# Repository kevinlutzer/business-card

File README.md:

# Electronic Business Card 

The purpose of this project was to demonstrate some of my skills as an Electrical Engineer to potential employers. This project required me to build and prototype a tri-state circuit, add controls with a STM32G ARM microcontroller and design/manufacture a custom printed circuit board. When you plug the device into a standard USB2A port it scrolls my portfolio website's URL across the matrix display. I designed this device to cost about $2.50 CAD per populated board. 

This idea was inspired by a piece of advice that Dave Jones, the owner of the [EEVblog](https://www.eevblog.com/) gave. He suggests that engineers should be bringing something to an interview to show that they can actually design and build things. I sent a later version of this project to Dave Jones with a programmer PCB which he opened on a [Mailbag Segment](https://youtu.be/45C6HFf2kIA?si=SCQMgJs3VvQc_wUq&t=3084). 

Currently I am using the project as a way to test and calibrate a pick and place machine.

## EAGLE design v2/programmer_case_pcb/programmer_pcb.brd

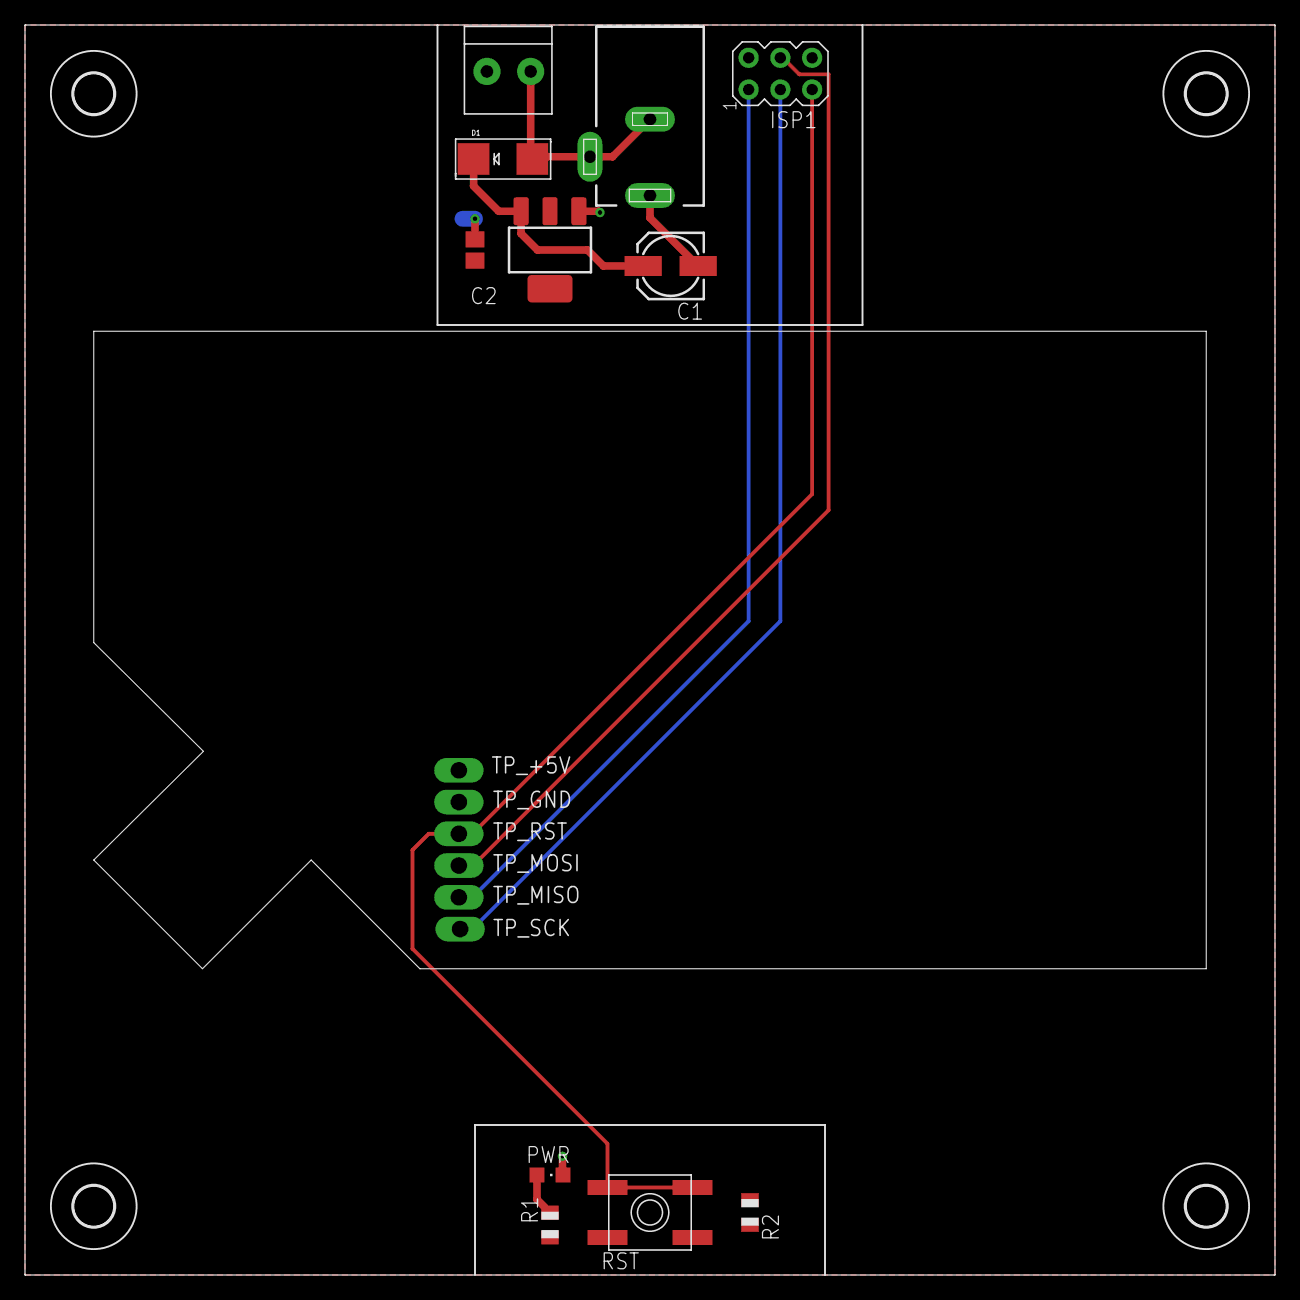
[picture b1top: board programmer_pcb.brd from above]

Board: 2 copper layers, 100.0 x 100.0 mm, 21 parts (0 on the bottom side), 9 nets.

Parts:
5VREG: LD1117; SOT223
C1: 0.33u; 153CLV-0505
C2: 0.1u; C0805
D1: SMADIODE
H1, H2, H3, H4: MOUNT-HOLE3.2; 3,2
ISP1: AVRISP-6; AVRISP
J1: 1X2-3.5MM
J2: DCJ0303
PWR: CHIPLED_0805
R1: 10K; R0805
R2: 220; R0805
RST: SPST_TACT-EVQQ2; EVQ-Q2
TP_+5V: TPSQPAD1-13Y; P1-13Y
TP_GND: TPSQPAD1-13Y; P1-13Y
TP_MISO: TPSQPAD1-13Y; P1-13Y
TP_MOSI: TPSQPAD1-13Y; P1-13Y
TP_RST: TPSQPAD1-13Y; P1-13Y
TP_SCK: TPSQPAD1-13Y; P1-13Y

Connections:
+5V: 5VREG.2, 5VREG.4, C2.1, ISP1.2, R1.2, R2.2, TP_+5V.TP
GND: 5VREG.1, C1.-, C2.2, ISP1.6, J1.1, J2.1, PWR.C, RST.A, RST.A', TP_GND.TP
MISO: ISP1.1, TP_MISO.TP
MOSI: ISP1.4, TP_MOSI.TP
unnamed: PWR.A, R1.1
unnamed: D1.A, J1.2, J2.2, J2.3
RESET: ISP1.5, R2.1, RST.B, RST.B', TP_RST.TP
SCK: ISP1.3, TP_SCK.TP
V+: 5VREG.3, C1.+, D1.C

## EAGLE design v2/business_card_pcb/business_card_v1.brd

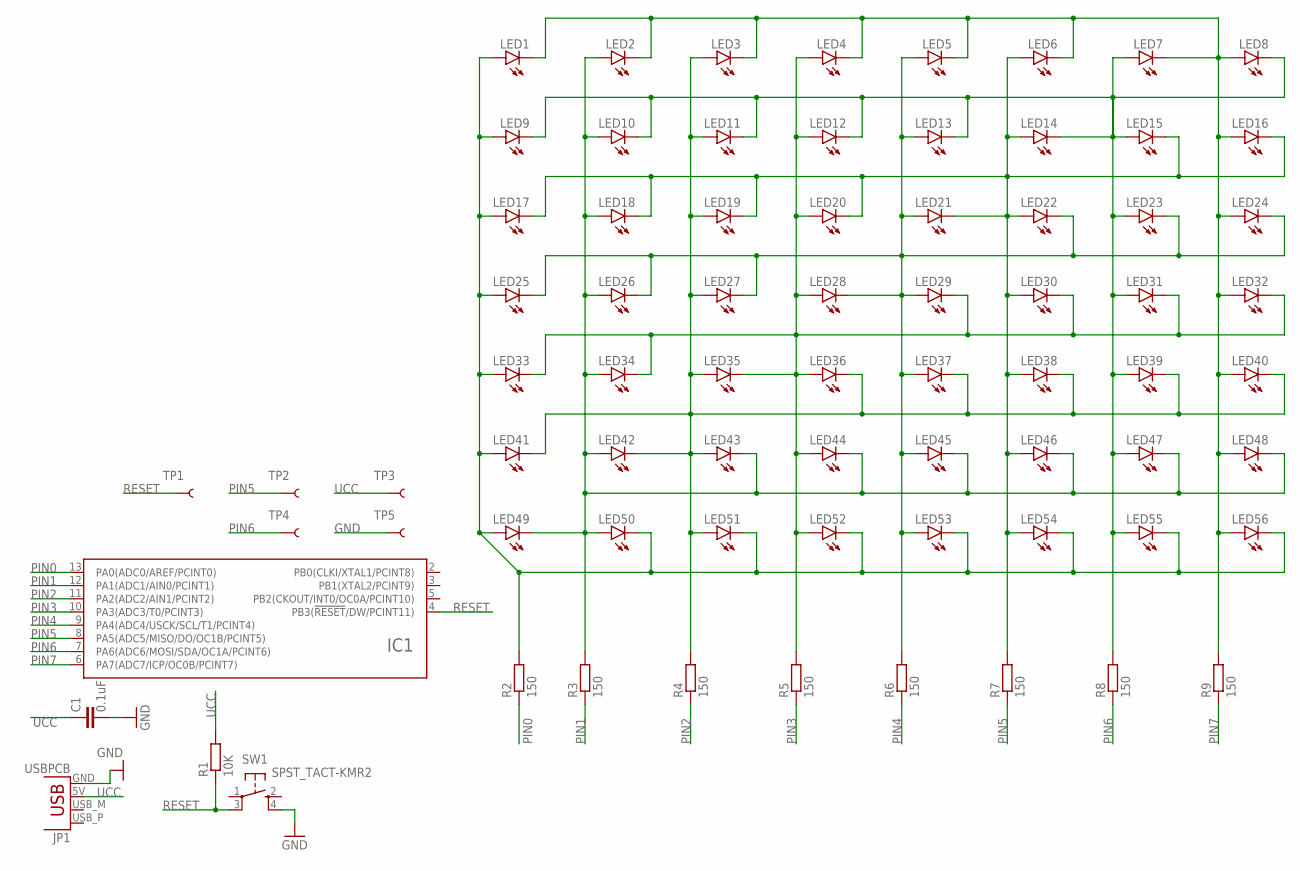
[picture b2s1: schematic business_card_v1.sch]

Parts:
C1: 0.1uF; C0805
IC1: ATTINY24/44/84-SSU; SOIC14
JP1: USBPCB; USB-A-PCB
LED1, LED2, LED3, LED4, LED5, LED6, LED7, LED8, LED9, LED10, LED11, LED12, LED13, LED14, LED15, LED16, LED17, LED18, LED19, LED20, LED21, LED22, LED23, LED24, LED25, LED26, LED27, LED28, LED29, LED30, LED31, LED32, LED33, LED34, LED35, LED36, LED37, LED38, LED39, LED40, LED41, LED42, LED43, LED44, LED45, LED46, LED47, LED48, LED49, LED50, LED51, LED52, LED53, LED54, LED55, LED56: LEDCHIPLED_0805; CHIPLED_0805
R1: 10K; R0805
R2, R3, R4, R5, R6, R7, R8, R9: 150; R0805
SW1: SPST_TACT-KMR2; KMR2
TP1, TP2, TP3, TP4, TP5: TEST-POINTPOGO_PTH; 1X01_NO_SILK

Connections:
GND: C1.2, IC1.14 (GND), JP1.GND, SW1.4 (S1), TP5.1
unnamed: LED1.A, LED9.A, LED17.A, LED25.A, LED33.A, LED41.A, LED49.A, LED50.C, LED51.C, LED52.C, LED53.C, LED54.C, LED55.C, LED56.C, R2.2
unnamed: LED2.A, LED10.A, LED18.A, LED26.A, LED34.A, LED42.A, LED43.C, LED44.C, LED45.C, LED46.C, LED47.C, LED48.C, LED49.C, LED50.A, R3.2
unnamed: LED3.A, LED11.A, LED19.A, LED27.A, LED35.A, LED36.C, LED37.C, LED38.C, LED39.C, LED40.C, LED41.C, LED42.C, LED43.A, LED51.A, R4.2
unnamed: LED4.A, LED12.A, LED20.A, LED28.A, LED29.C, LED30.C, LED31.C, LED32.C, LED33.C, LED34.C, LED35.C, LED36.A, LED44.A, LED52.A, R5.2
unnamed: LED1.C, LED2.C, LED3.C, LED4.C, LED5.C, LED6.C, LED7.C, LED8.A, LED16.A, LED24.A, LED32.A, LED40.A, LED48.A, LED56.A, R9.2
unnamed: LED7.A, LED8.C, LED9.C, LED10.C, LED11.C, LED12.C, LED13.C, LED14.C, LED15.A, LED23.A, LED31.A, LED39.A, LED47.A, LED55.A, R8.2
unnamed: LED6.A, LED14.A, LED15.C, LED16.C, LED17.C, LED18.C, LED19.C, LED20.C, LED21.C, LED22.A, LED30.A, LED38.A, LED46.A, LED54.A, R7.2
unnamed: LED5.A, LED13.A, LED21.A, LED22.C, LED23.C, LED24.C, LED25.C, LED26.C, LED27.C, LED28.C, LED29.A, LED37.A, LED45.A, LED53.A, R6.2
PIN0: IC1.13 (PA0(ADC0/AREF/PCINT0)), R2.1
PIN1: IC1.12 (PA1(ADC1/AIN0/PCINT1)), R3.1
PIN2: IC1.11 (PA2(ADC2/AIN1/PCINT2)), R4.1
PIN3: IC1.10 (PA3(ADC3/T0/PCINT3)), R5.1
PIN4: IC1.9 (PA4(ADC4/USCK/SCL/T1/PCINT4)), R6.1
PIN5: IC1.8 (PA5(ADC5/MISO/DO/OC1B/PCINT5)), R7.1, TP2.1
PIN6: IC1.7 (PA6(ADC6/MOSI/SDA/OC1A/PCINT6)), R8.1, TP4.1
PIN7: IC1.6 (PA7(ADC7/ICP/OC0B/PCINT7)), R9.1
RESET: IC1.4 (PB3(!RESET!/DW/PCINT11)), R1.1, SW1.3 (P1), TP1.1
UCC: C1.1, IC1.1 (UCC), JP1.5V (VBUS), R1.2, TP3.1

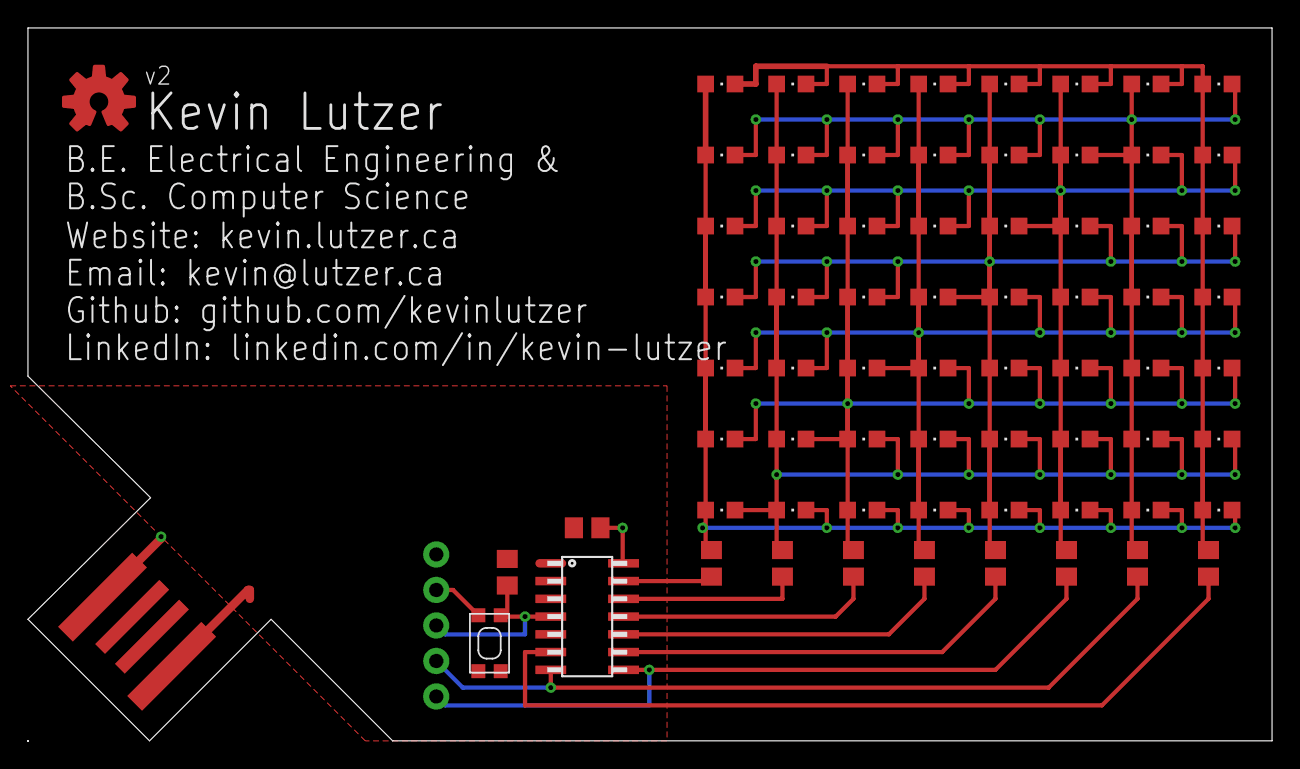
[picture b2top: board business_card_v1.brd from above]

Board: 2 copper layers, 89.0 x 51.0 mm, 75 parts (0 on the bottom side), 19 nets.

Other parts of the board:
U$1: OSHWLOGO_TOP_0.2

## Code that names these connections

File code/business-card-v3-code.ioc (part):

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PA6.GPIOParameters=PinState,GPIO_Label
Mcu.UserName=STM32G030F6Px
PA0.PinState=GPIO_PIN_RESET
PA0.GPIO_Label=PINA
PA3.GPIOParameters=GPIO_Label
PA6.PinState=GPIO_PIN_RESET
PA6.GPIO_Label=PING
PA2.GPIOParameters=GPIO_Label
PA7.PinState=GPIO_PIN_RESET
PA1.Signal=GPIO_Output
PA5.Signal=GPIO_Output
RCC.HSE_VALUE=8000000
PA4.GPIO_PuPd=GPIO_NOPULL
board=custom
PA1.GPIOParameters=GPIO_Label
PA1.GPIO_Label=PINB
PA4.GPIOParameters=GPIO_PuPd,GPIO_Label
Mcu.Name=STM32G030F6Px
PA2.Signal=GPIO_Output
PA0.Signal=GPIO_Output
PA4.Signal=GPIO_Output
RCC.SYSCLKFreq_VALUE=16000000
Mcu.Package=TSSOP20
PA6.Signal=GPIO_Output
PA7.GPIO_Label=PINH
PA5.GPIO_Label=PINF
PA2.GPIO_Label=PINC
PA0.GPIOParameters=PinState,GPIO_Label
PA5.GPIOParameters=GPIO_Label
PA4.GPIO_Label=PINE
PA7.GPIOParameters=PinState,GPIO_Label
PA3.GPIO_Label=PIND
PA3.Signal=GPIO_Output
PA7.Signal=GPIO_Output

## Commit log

2016-05-23 adding code and cad files to the repository
2016-07-15 deleted lock on .sch file
2016-07-15 changed folder names
2017-04-01 last commit before computer reset
2019-02-21 refactor and put everything in a v1
2020-01-19 add the base pcb files for the v2 design
2020-02-07 get the led layout right
2020-02-07 update pcb and schematic
2020-02-09 route the led grid, add the silk screen
2020-02-10 finish of the routing and get personal information on silk screen
2020-02-10 fix the business card design
2020-02-10 business card
2020-02-10 get the business card design done, looking for review now
2020-02-10 fix some of the silk screen
2020-02-10 add the gerber files
2020-02-11 more silk screen updates
2020-02-11 get the businss card completed
2020-02-11 update the 3d models
2020-02-12 update cards
2020-02-12 move the pcb_business_card
2020-02-13 remove DS_store
2020-02-13 add some text describing the business card project
2020-02-13 update to add the v1 and v2 board images
2020-02-13 add the what does it do section
2020-02-13 typo
2020-02-13 more typos
2020-02-18 get the published version completed
2020-03-03 refactor the readme, update project file
2020-03-04 try and setup the leds' gp
2020-03-04 more progress
2020-03-04 add the vstore code workspace file
2020-03-04 try and use the binary mehtod
2020-03-13 cleanup the code and remove the old constant
2020-03-13 update the code
2020-03-13 add the pcb boarder
2020-03-14 add the programming enclosure
2020-03-14 add the programmer case base file
2020-03-14 revert some changes to the v1 directory
2020-03-16 switch everything over to use cloud storage
2020-03-31 add the programming case
2020-03-31 name change of the business card PCB
2020-03-31 add the sck pad pin for miso and mosi
2020-03-31 add the zip file
2020-03-31 programmer pcb schematic
2020-03-31 finish the schematic
2020-03-31 start the pcb
2020-04-01 start populating some of the components
2020-04-02 finish the design
2020-04-02 add zip with gerber files
2020-05-04 add the v3 version of the pcb
2020-05-05 add the base import of the business card files
2020-05-07 finish pcb prototype for the card
2020-05-07 add code
2020-05-08 add the final touches to the Pcb
2020-05-09 add dimensions
2020-05-09 move everything before business-card-v3-pcb
2020-05-09 add the gerbers
2020-05-09 build out the majority of the board
2020-05-09 finish the pcb design
2020-05-10 move the programmer board files up a level
2020-05-10 regen all gerbers
2020-05-10 update to use a smaller resistor array
2020-05-14 add gerber files for the pcb
2020-05-14 move folders around to the top layer
2020-05-14 move the charlie_plexing files to the new business card code folder
2020-05-14 rename folders to be more generic
2020-05-14 move gerbers into the gerber folder for v3 design
2020-05-14 move gerbers around
2020-05-14 move gerber names around
2020-05-14 add gerbers for v2 and v3 programmers
2020-05-14 remove the v2 and v1 folder
2020-05-14 remove uneeded v3
2020-05-14 remove the gerber files
2020-05-14 cleanup
2020-05-24 bring back the correct revision of the v3 pcb
2020-05-24 remove the v3
2020-05-24 remove the gerber folder as I am using one at a different level
2020-05-24 remove the empty frame
2020-05-24 remove pcb footprints that are not needed
2020-05-24 remove the rescue library
2020-05-24 remove the rescue lib folder
2020-05-26 update the project config to have the correct outputs
2020-07-02 update code
2020-07-11 add the functions to display the leds correctly
2020-07-12 get a hi and smiley face working
2020-07-12 regen the Cubemx project
2020-07-12 update the source
2020-08-06 update card to v4
2020-08-06 create a net and update version of file names
2020-08-06 update pcb gerbers
2020-08-08 add the gerbers for the pcb programmer
2020-08-08 update the gerbers for the programemr pcb
2023-07-24 realign components on 0.01 inch grid, use solely kicad parts not eagle parts
2023-07-24 remove the progremmwer and the eagle files, rename everything to just business card
2023-07-24 make the v4 gerbers and ibom
2023-08-06 add updates
2023-10-07 rename documentation to assets
2023-10-07 remove business_card_v1 files
2023-10-07 use leds instead, add bom, update code
2023-10-07 add fab
2023-10-07 update changelog and readme
2023-10-07 use the LED footprint instead of diode footprint for LED2
2023-10-07 update and add some assets

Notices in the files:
parts and their libraries:
SparkFun-Connectors: Licensing: Creative Commons ShareAlike 4.0 International - https://creativecommons.org/licenses/by-sa/4.0
